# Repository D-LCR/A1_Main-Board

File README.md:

# D-LCR_A1_Main-Board
LCR Meter Analogue Main Board

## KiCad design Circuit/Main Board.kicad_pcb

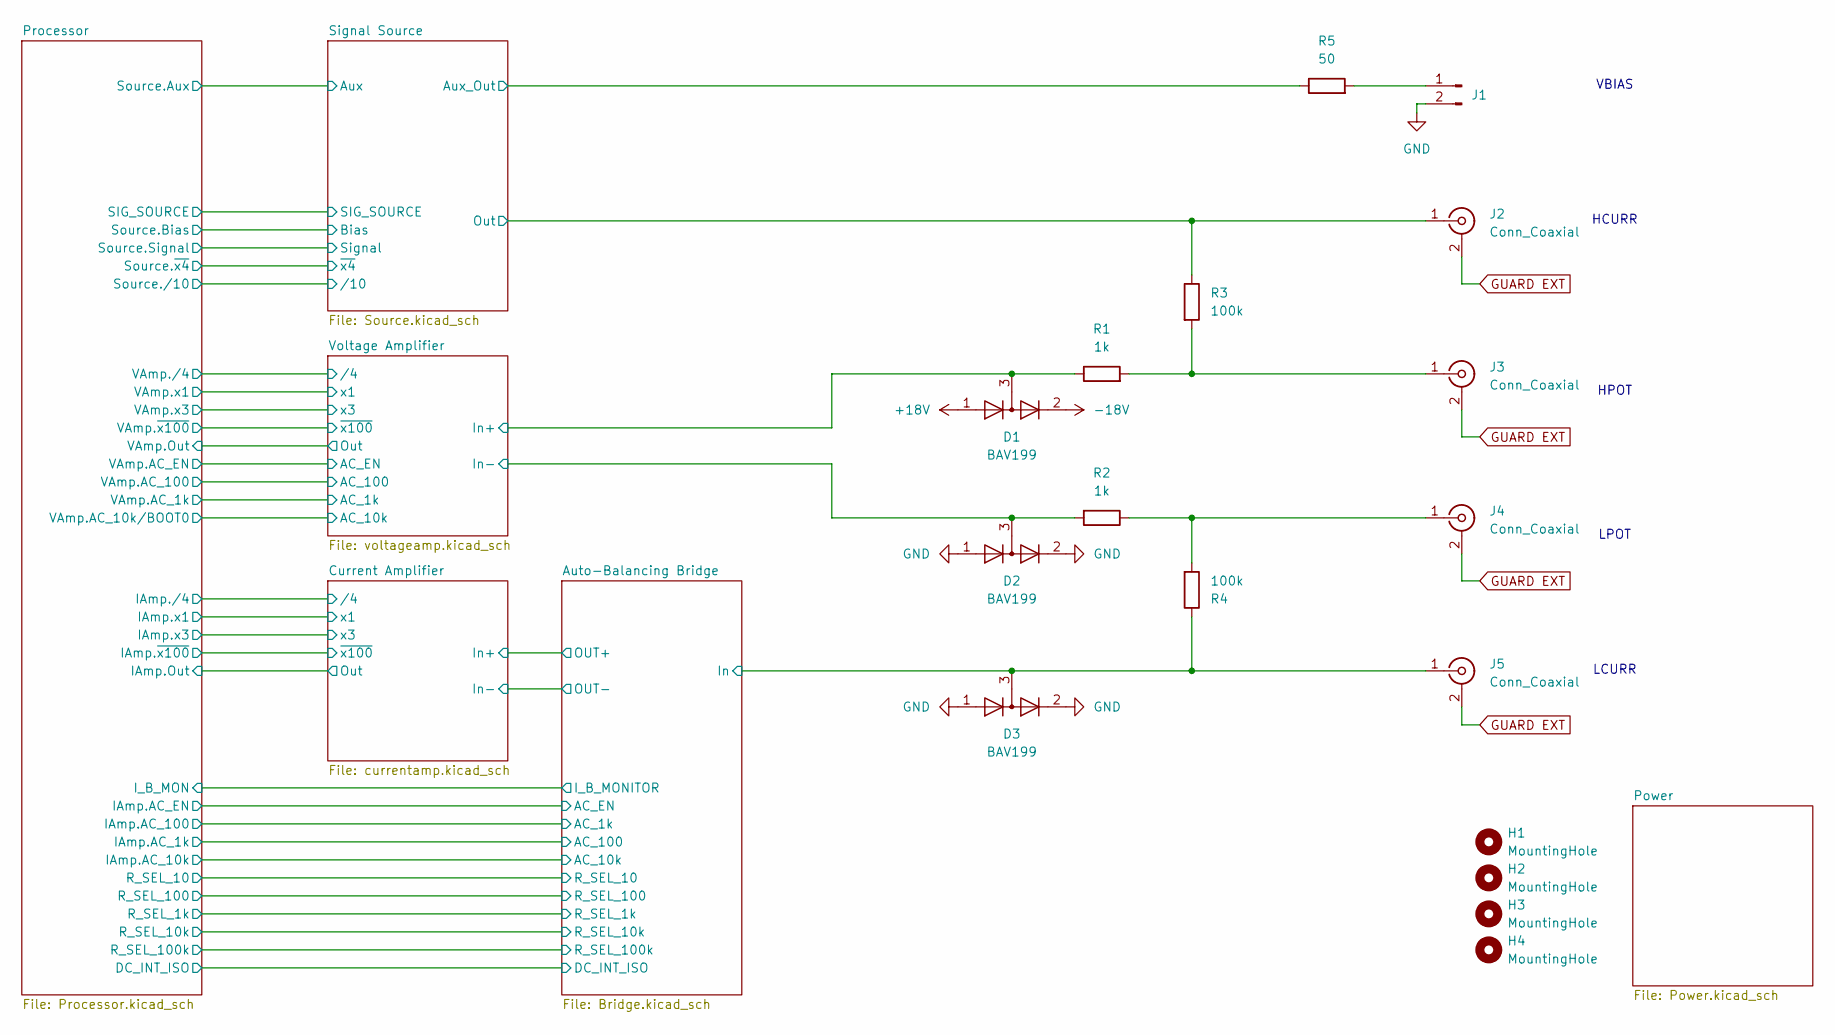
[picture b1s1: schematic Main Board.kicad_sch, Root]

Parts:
D1, D2, D3: BAV199; SOT-23
H1, H2, H3, H4: MountingHole; MountingHole_3.2mm_M3
J1: Conn_01x02_Pin; Molex_KK-254_AE-6410-02A_1x02_P2.54mm_Vertical
J2, J3, J4, J5: Conn_Coaxial; BNC_Amphenol_B6252HB-NPP3G-50_Horizontal
R1, R2: 1k; R_0805_2012Metric
R3, R4: 100k; R_0805_2012Metric
R5: 50; R_0805_2012Metric

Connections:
+18V: D1.1 (K); also elsewhere on the board
-18V: D1.2 (A); also elsewhere on the board
/Auto-Balancing Bridge/TIA_SUM: D3.3 (K), J5.1 (In), R4.1; also elsewhere on the board
/Signal Source/Aux_Out: R5.1; also elsewhere on the board
/Signal Source/Out: J2.1 (In), R3.1; also elsewhere on the board
/Voltage Amplifier/In+: D1.3 (K), R1.1; also elsewhere on the board
/Voltage Amplifier/In-: D2.3 (K), R2.2; also elsewhere on the board
GND: D2.1 (K), D2.2 (A), D3.1 (K), D3.2 (A), J1.2; also elsewhere on the board
GUARD EXT: J2.2 (Ext), J3.2 (Ext), J4.2 (Ext), J5.2 (Ext); also elsewhere on the board
unnamed: J1.1, R5.2
unnamed: J3.1 (In), R1.2, R3.2
unnamed: J4.1 (In), R2.1, R4.2

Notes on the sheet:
LPOT
HCURR
VBIAS
LCURR
HPOT

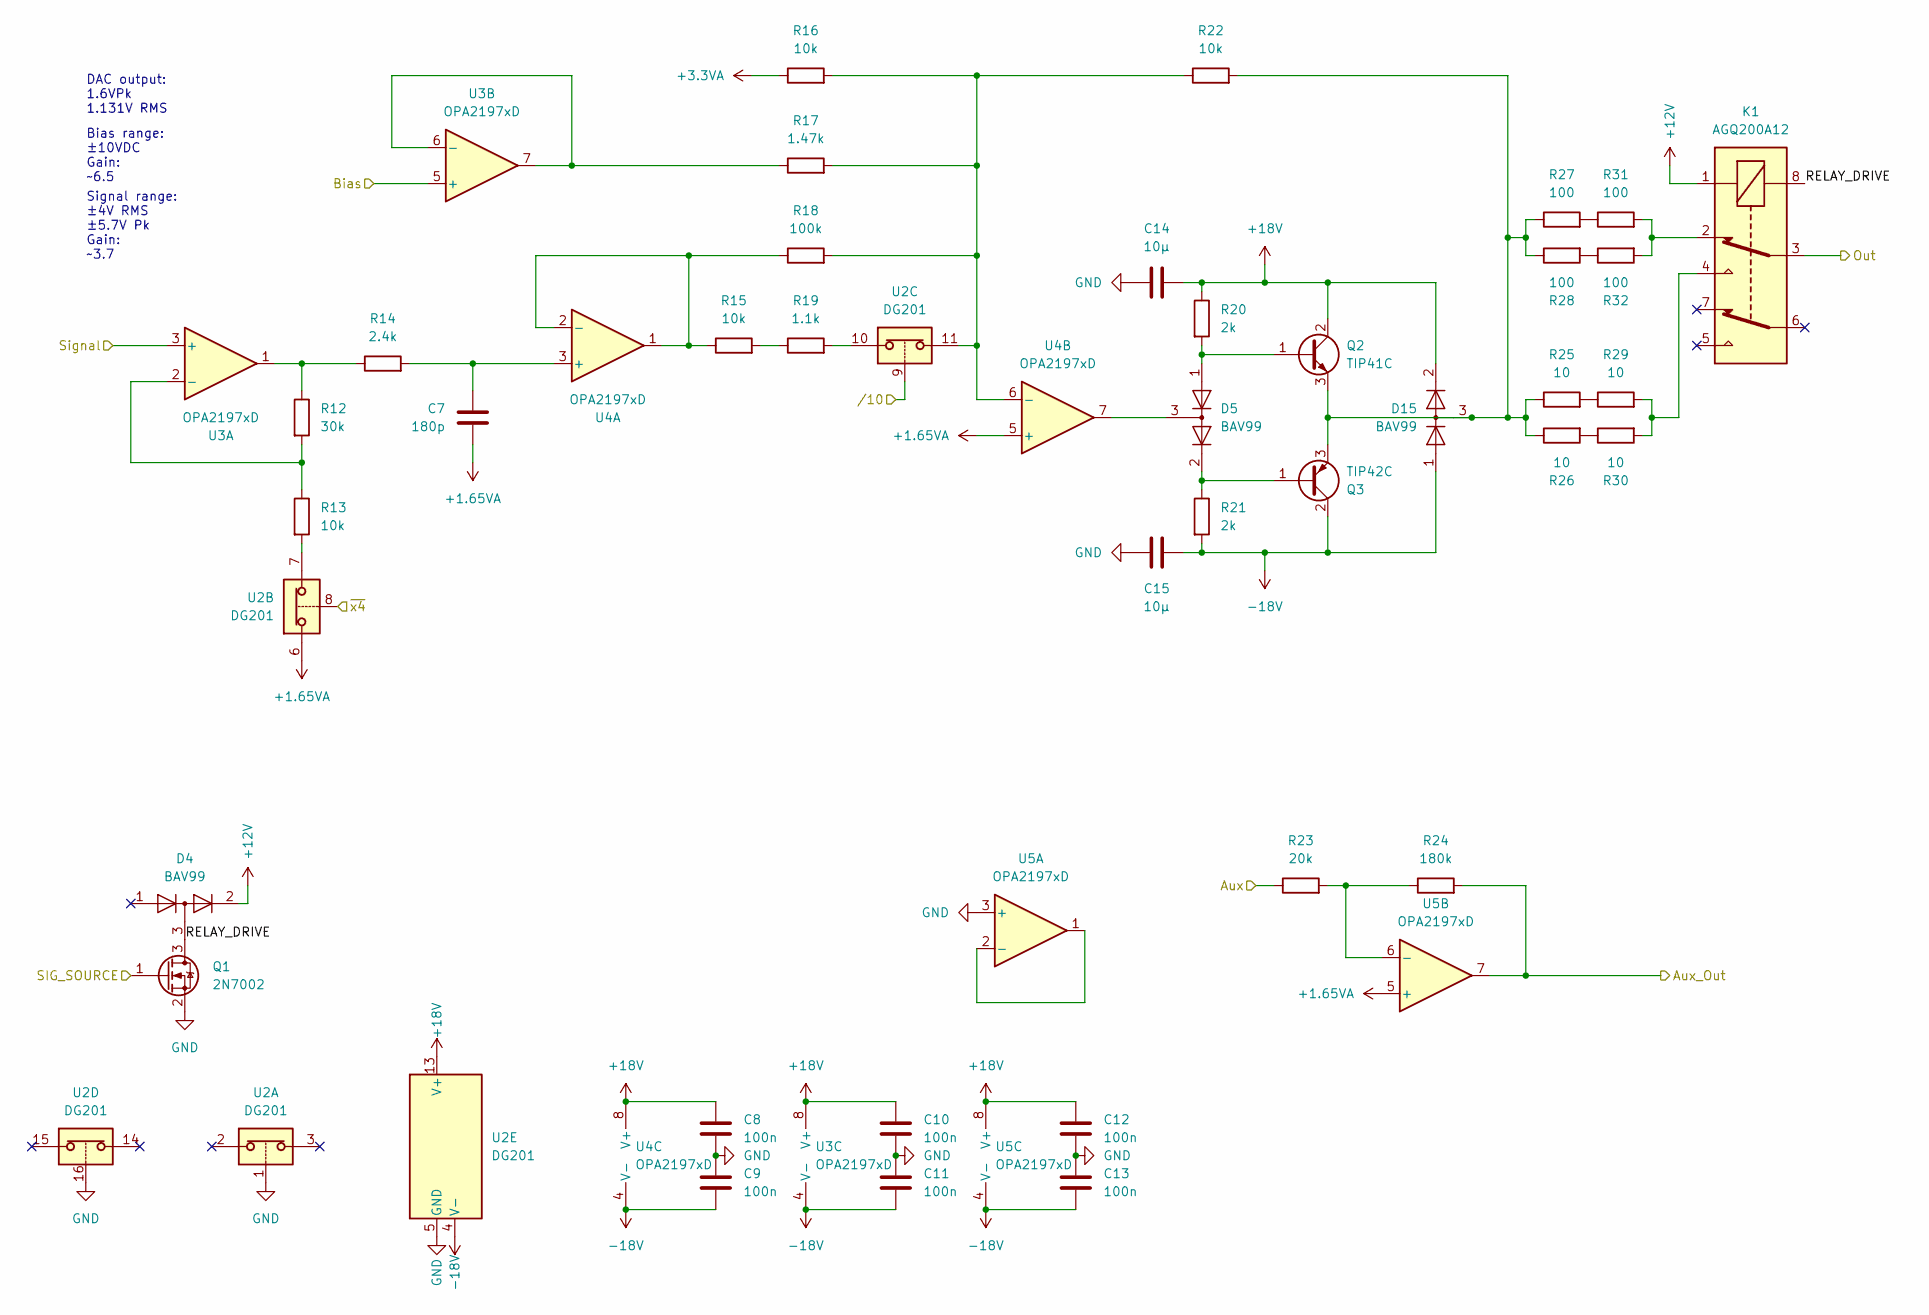
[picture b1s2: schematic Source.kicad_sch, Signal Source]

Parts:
C7: 180p; C_0805_2012Metric
C8, C9, C10, C11, C12, C13: 100n; C_0805_2012Metric
C14, C15: 10µ; C_0805_2012Metric
D4, D5, D15: BAV99; SOT-23
K1: AGQ200A12; RELAY_AGQ_A_PAN; Mouser Part Number 769-AGQ200A12
Q1: 2N7002; SOT-23
Q2: TIP41C; TO-220-3_Vertical
Q3: TIP42C; TO-220-3_Vertical
R12: 30k; R_0805_2012Metric
R13, R15, R16, R22: 10k; R_0805_2012Metric
R14: 2.4k; R_0805_2012Metric
R17: 1.47k; R_0805_2012Metric
R18: 100k; R_0805_2012Metric
R19: 1.1k; R_0805_2012Metric
R20, R21: 2k; R_0805_2012Metric
R23: 20k; R_0805_2012Metric
R24: 180k; R_0805_2012Metric
R25, R26, R29, R30: 10; R_2512_6332Metric
R27, R28, R31, R32: 100; R_0805_2012Metric
U2: DG201; SOIC-16_3.9x9.9mm_P1.27mm
U3, U4, U5: OPA2197xD; SOIC-8_3.9x4.9mm_P1.27mm

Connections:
+1.65VA: C7.2, U2.6, U4.5 (+), U5.5 (+); also elsewhere on the board
+3.3VA: R16.1; also elsewhere on the board
+12V: D4.2 (A), K1.1; also elsewhere on the board
+18V: C8.1, C10.1, C12.1, C14.2, D15.2 (A), Q2.2 (C), R20.1, U2.13 (V+), U3.8 (V+), U4.8 (V+), U5.8 (V+); also elsewhere on the board
-18V: C9.2, C11.2, C13.2, C15.2, D15.1 (K), Q3.2 (C), R21.2, U2.4 (V-), U3.4 (V-), U4.4 (V-), U5.4 (V-); also elsewhere on the board
/Processor/SIG_SOURCE: Q1.1 (G); also elsewhere on the board
/Processor/Source.Aux: R23.1; also elsewhere on the board
/Processor/Source.Bias: U3.5 (+); also elsewhere on the board
/Processor/Source.Signal: U3.3 (+); also elsewhere on the board
/Processor/Source./10: U2.9; also elsewhere on the board
/Processor/Source.~x4: U2.8; also elsewhere on the board
/Signal Source/Aux_Out: R24.2, U5.7; also elsewhere on the board
/Signal Source/Out: K1.3; also elsewhere on the board
/Signal Source/RELAY_DRIVE: D4.3 (K), K1.8, Q1.3 (D)
GND: C8.2, C9.1, C10.2, C11.1, C12.2, C13.1, C14.1, C15.1, Q1.2 (S), U2.1, U2.5 (GND), U2.16, U5.3 (+); also elsewhere on the board
unnamed: D5.2 (A), Q3.1 (B), R21.1
unnamed: D5.3 (K), U4.7
unnamed: K1.2, R31.2, R32.2
unnamed: K1.4, R29.2, R30.2
unnamed: D5.1 (K), Q2.1 (B), R20.2
unnamed: D15.3 (K), Q2.3 (E), Q3.3 (E), R22.2, R25.1, R26.1, R27.1, R28.1
unnamed: R12.1, R14.1, U3.1
unnamed: R13.2, U2.7
unnamed: R15.2, R19.1
unnamed: R19.2, U2.10
unnamed: R25.2, R29.1
unnamed: R26.2, R30.1
unnamed: R27.2, R31.1
unnamed: R28.2, R32.1
unnamed: R12.2, R13.1, U3.2 (-)
unnamed: R17.1, U3.6 (-), U3.7
unnamed: C7.1, R14.2, U4.3 (+)
unnamed: R15.1, R18.1, U4.1, U4.2 (-)
unnamed: R16.2, R17.2, R18.2, R22.1, U2.11, U4.6 (-)
unnamed: U5.1, U5.2 (-)
unnamed: R23.2, R24.1, U5.6 (-)

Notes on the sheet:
Bias range: ±10VDC Gain: ~6.5
DAC output: 1.6VPk 1.131V RMS
Signal range: ±4V RMS ±5.7V Pk Gain: ~3.7

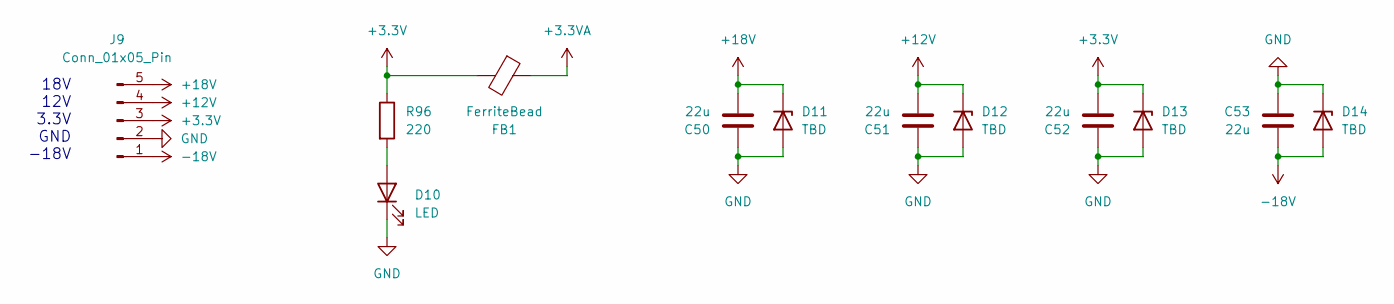
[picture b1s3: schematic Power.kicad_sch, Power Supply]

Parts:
C50, C51, C52, C53: 22u; C_1210_3225Metric
D10: LED; LED_0805_2012Metric
D11, D12, D13, D14: TBD; D_SMA
FB1: FerriteBead; L_0805_2012Metric
J9: Conn_01x05_Pin; Molex_KK-254_AE-6410-05A_1x05_P2.54mm_Vertical
R96: 220; R_0805_2012Metric

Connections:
+3.3V: C52.2, D13.1 (K), FB1.2, J9.3, R96.1; also elsewhere on the board
+3.3VA: FB1.1; also elsewhere on the board
+12V: C51.2, D12.1 (K), J9.4; also elsewhere on the board
+18V: C50.2, D11.1 (K), J9.5; also elsewhere on the board
-18V: C53.1, D14.2 (A), J9.1; also elsewhere on the board
GND: C50.1, C51.1, C52.1, C53.2, D10.1 (K), D11.2 (A), D12.2 (A), D13.2 (A), D14.1 (K), J9.2; also elsewhere on the board
unnamed: D10.2 (A), R96.2

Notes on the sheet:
18V 12V 3.3V GND -18V

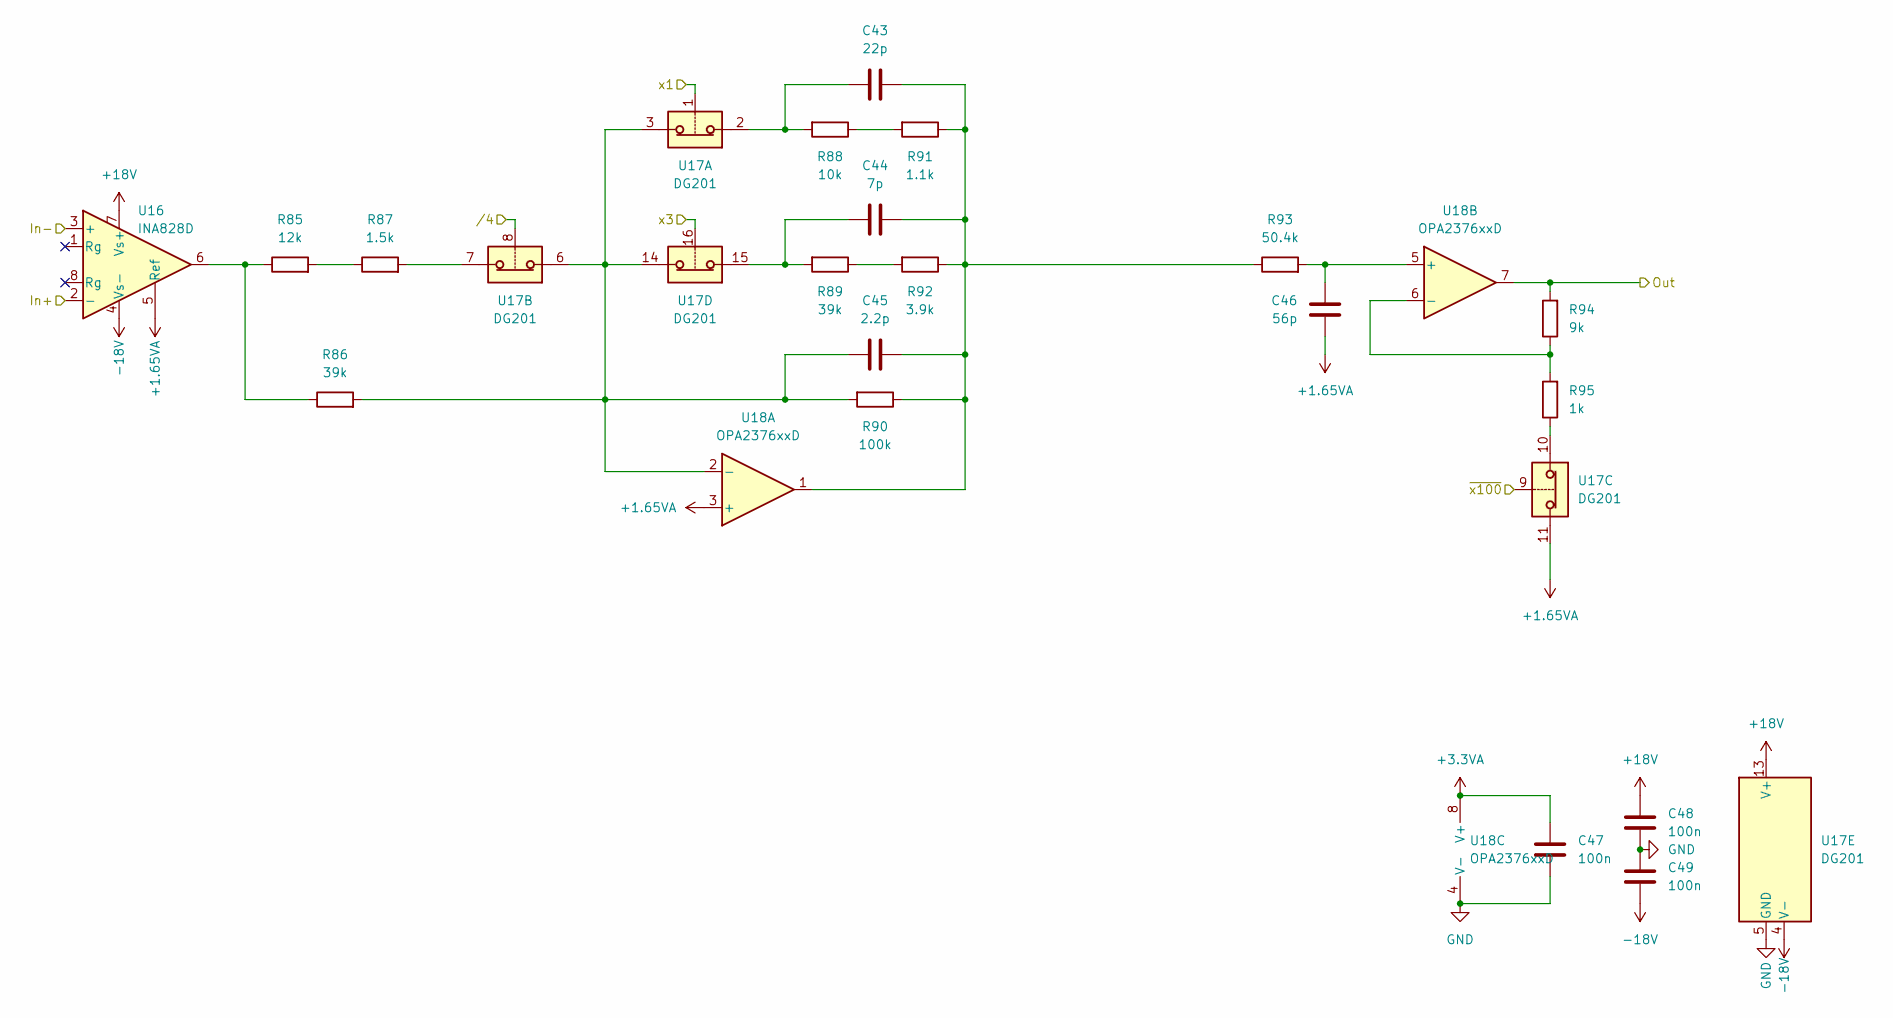
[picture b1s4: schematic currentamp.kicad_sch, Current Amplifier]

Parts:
C43: 22p; C_0805_2012Metric
C44: 7p; C_0805_2012Metric
C45: 2.2p; C_0805_2012Metric
C46: 56p; C_0805_2012Metric
C47, C48, C49: 100n; C_0805_2012Metric
R85: 12k; R_0805_2012Metric
R86, R89: 39k; R_0805_2012Metric
R87: 1.5k; R_0805_2012Metric
R88: 10k; R_0805_2012Metric
R90: 100k; R_0805_2012Metric
R91: 1.1k; R_0805_2012Metric
R92: 3.9k; R_0805_2012Metric
R93: 50.4k; R_0805_2012Metric
R94: 9k; R_0805_2012Metric
R95: 1k; R_0805_2012Metric
U16: INA828D; SOIC-8_3.9x4.9mm_P1.27mm
U17: DG201; SOIC-16_3.9x9.9mm_P1.27mm
U18: OPA2376xxD; SOIC-8_3.9x4.9mm_P1.27mm

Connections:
+1.65VA: C46.2, U16.5 (Ref), U17.11, U18.3 (+); also elsewhere on the board
+3.3VA: C47.1, U18.8 (V+); also elsewhere on the board
+18V: C48.1, U16.7 (Vs+), U17.13 (V+); also elsewhere on the board
-18V: C49.2, U16.4 (Vs-), U17.4 (V-); also elsewhere on the board
/Auto-Balancing Bridge/OUT+: U16.2 (-); also elsewhere on the board
/Auto-Balancing Bridge/TIA_SUM: U16.3 (+); also elsewhere on the board
/Current Amplifier/Out: R94.2, U18.7; also elsewhere on the board
/Current Amplifier/x1: U17.1; also elsewhere on the board
/Current Amplifier/x3: U17.16; also elsewhere on the board
/Current Amplifier//4: U17.8; also elsewhere on the board
/Current Amplifier/~x100: U17.9; also elsewhere on the board
GND: C47.2, C48.2, C49.1, U17.5 (GND), U18.4 (V-); also elsewhere on the board
unnamed: C43.1, R88.2, U17.2
unnamed: C43.2, C44.2, C45.2, R90.1, R91.1, R92.1, R93.1, U18.1
unnamed: C44.1, R89.2, U17.15
unnamed: R85.1, R86.1, U16.6
unnamed: R85.2, R87.1
unnamed: R87.2, U17.7
unnamed: R88.1, R91.2
unnamed: R89.1, R92.2
unnamed: R95.1, U17.10
unnamed: C45.1, R86.2, R90.2, U17.3, U17.6, U17.14, U18.2 (-)
unnamed: C46.1, R93.2, U18.5 (+)
unnamed: R94.1, R95.2, U18.6 (-)

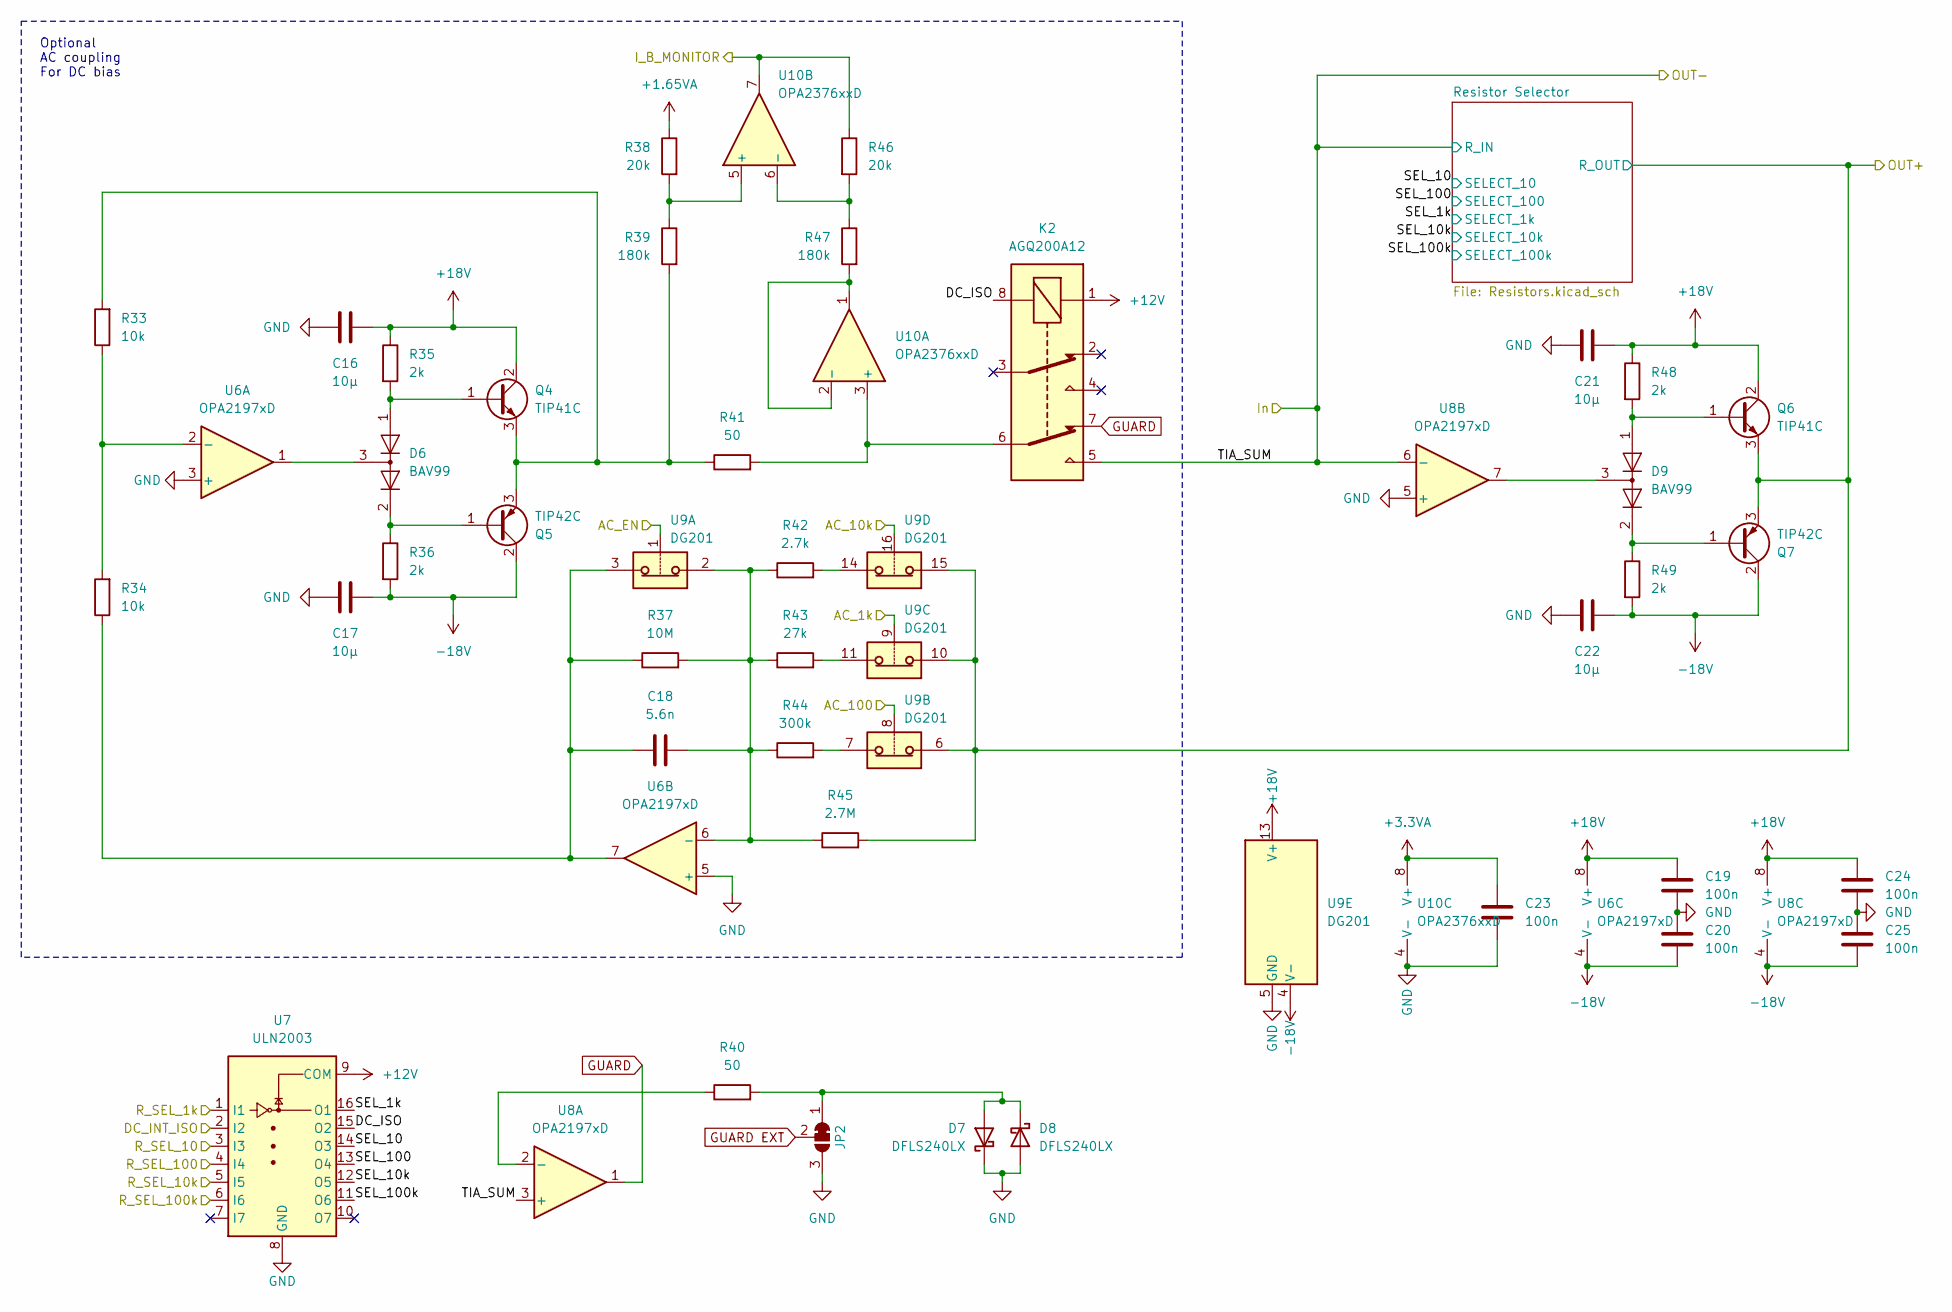
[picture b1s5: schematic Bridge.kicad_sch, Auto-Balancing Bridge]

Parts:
C16, C17, C21, C22: 10µ; C_0805_2012Metric
C18: 5.6n; C_0805_2012Metric
C19, C20, C23, C24, C25: 100n; C_0805_2012Metric
D6, D9: BAV99; SOT-23
D7, D8: DFLS240LX; D_PowerDI-123
JP2: SolderJumper_3_Bridged12; SolderJumper-3_P1.3mm_Bridged12_RoundedPad1.0x1.5mm
K2: AGQ200A12; RELAY_AGQ_A_PAN; Mouser Part Number 769-AGQ200A12
Q4, Q6: TIP41C; TO-220-3_Vertical
Q5, Q7: TIP42C; TO-220-3_Vertical
R33, R34: 10k; R_0805_2012Metric
R35, R36, R48, R49: 2k; R_0805_2012Metric
R37: 10M; R_0805_2012Metric
R38, R46: 20k; R_0805_2012Metric
R39, R47: 180k; R_0805_2012Metric
R40, R41: 50; R_0805_2012Metric
R42: 2.7k; R_0805_2012Metric
R43: 27k; R_0805_2012Metric
R44: 300k; R_0805_2012Metric
R45: 2.7M; R_0805_2012Metric
U6, U8: OPA2197xD; SOIC-8_3.9x4.9mm_P1.27mm
U7: ULN2003; SOIC-16_3.9x9.9mm_P1.27mm
U9: DG201; SOIC-16_3.9x9.9mm_P1.27mm
U10: OPA2376xxD; SOIC-8_3.9x4.9mm_P1.27mm

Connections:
+1.65VA: R38.1; also elsewhere on the board
+3.3VA: C23.1, U10.8 (V+); also elsewhere on the board
+12V: K2.1, U7.9 (COM); also elsewhere on the board
+18V: C16.2, C19.1, C21.2, C24.1, Q4.2 (C), Q6.2 (C), R35.1, R48.1, U6.8 (V+), U8.8 (V+), U9.13 (V+); also elsewhere on the board
-18V: C17.2, C20.2, C22.2, C25.2, Q5.2 (C), Q7.2 (C), R36.2, R49.2, U6.4 (V-), U8.4 (V-), U9.4 (V-); also elsewhere on the board
/Auto-Balancing Bridge/AC_1k: U9.9; also elsewhere on the board
/Auto-Balancing Bridge/AC_10k: U9.16; also elsewhere on the board
/Auto-Balancing Bridge/AC_100: U9.8; also elsewhere on the board
/Auto-Balancing Bridge/AC_EN: U9.1; also elsewhere on the board
/Auto-Balancing Bridge/DC_INT_ISO: U7.2 (I2); also elsewhere on the board
/Auto-Balancing Bridge/DC_ISO: K2.8, U7.15 (O2)
/Auto-Balancing Bridge/I_B_MONITOR: R46.1, U10.7; also elsewhere on the board
/Auto-Balancing Bridge/OUT+: Q6.3 (E), Q7.3 (E), R45.2, U9.6, U9.10, U9.15; also elsewhere on the board
/Auto-Balancing Bridge/R_SEL_1k: U7.1 (I1); also elsewhere on the board
/Auto-Balancing Bridge/R_SEL_10: U7.3 (I3); also elsewhere on the board
/Auto-Balancing Bridge/R_SEL_10k: U7.5 (I5); also elsewhere on the board
/Auto-Balancing Bridge/R_SEL_100: U7.4 (I4); also elsewhere on the board
/Auto-Balancing Bridge/R_SEL_100k: U7.6 (I6); also elsewhere on the board
/Auto-Balancing Bridge/SEL_1k: U7.16 (O1); also elsewhere on the board
/Auto-Balancing Bridge/SEL_10: U7.14 (O3); also elsewhere on the board
/Auto-Balancing Bridge/SEL_10k: U7.12 (O5); also elsewhere on the board
/Auto-Balancing Bridge/SEL_100: U7.13 (O4); also elsewhere on the board
/Auto-Balancing Bridge/SEL_100k: U7.11 (O6); also elsewhere on the board
/Auto-Balancing Bridge/TIA_SUM: K2.5, U8.3 (+), U8.6 (-); also elsewhere on the board
GND: C16.1, C17.1, C19.2, C20.1, C21.1, C22.1, C23.2, C24.2, C25.1, D7.1 (K), D8.2 (A), JP2.3 (B), U6.3 (+), U6.5 (+), U7.8 (GND), U8.5 (+), U9.5 (GND), U10.4 (V-); also elsewhere on the board
GUARD: K2.7, U8.1; also elsewhere on the board
GUARD EXT: JP2.2 (C); also elsewhere on the board
unnamed: C18.1, R34.1, R37.1, U6.7, U9.3
unnamed: D6.2 (A), Q5.1 (B), R36.1
unnamed: D6.3 (K), U6.1
unnamed: D7.2 (A), D8.1 (K), JP2.1 (A), R40.2
unnamed: D9.2 (A), Q7.1 (B), R49.1
unnamed: D9.3 (K), U8.7
unnamed: D6.1 (K), Q4.1 (B), R35.2
unnamed: Q4.3 (E), Q5.3 (E), R33.2, R39.2, R41.1
unnamed: D9.1 (K), Q6.1 (B), R48.2
unnamed: R42.2, U9.14
unnamed: R43.2, U9.11
unnamed: R44.2, U9.7
unnamed: R33.1, R34.2, U6.2 (-)
unnamed: C18.2, R37.2, R42.1, R43.1, R44.1, R45.1, U6.6 (-), U9.2
unnamed: R40.1, U8.2 (-)
unnamed: K2.6, R41.2, U10.3 (+)
unnamed: R47.2, U10.1, U10.2 (-)
unnamed: R38.2, R39.1, U10.5 (+)
unnamed: R46.2, R47.1, U10.6 (-)

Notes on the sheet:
Optional AC coupling For DC bias

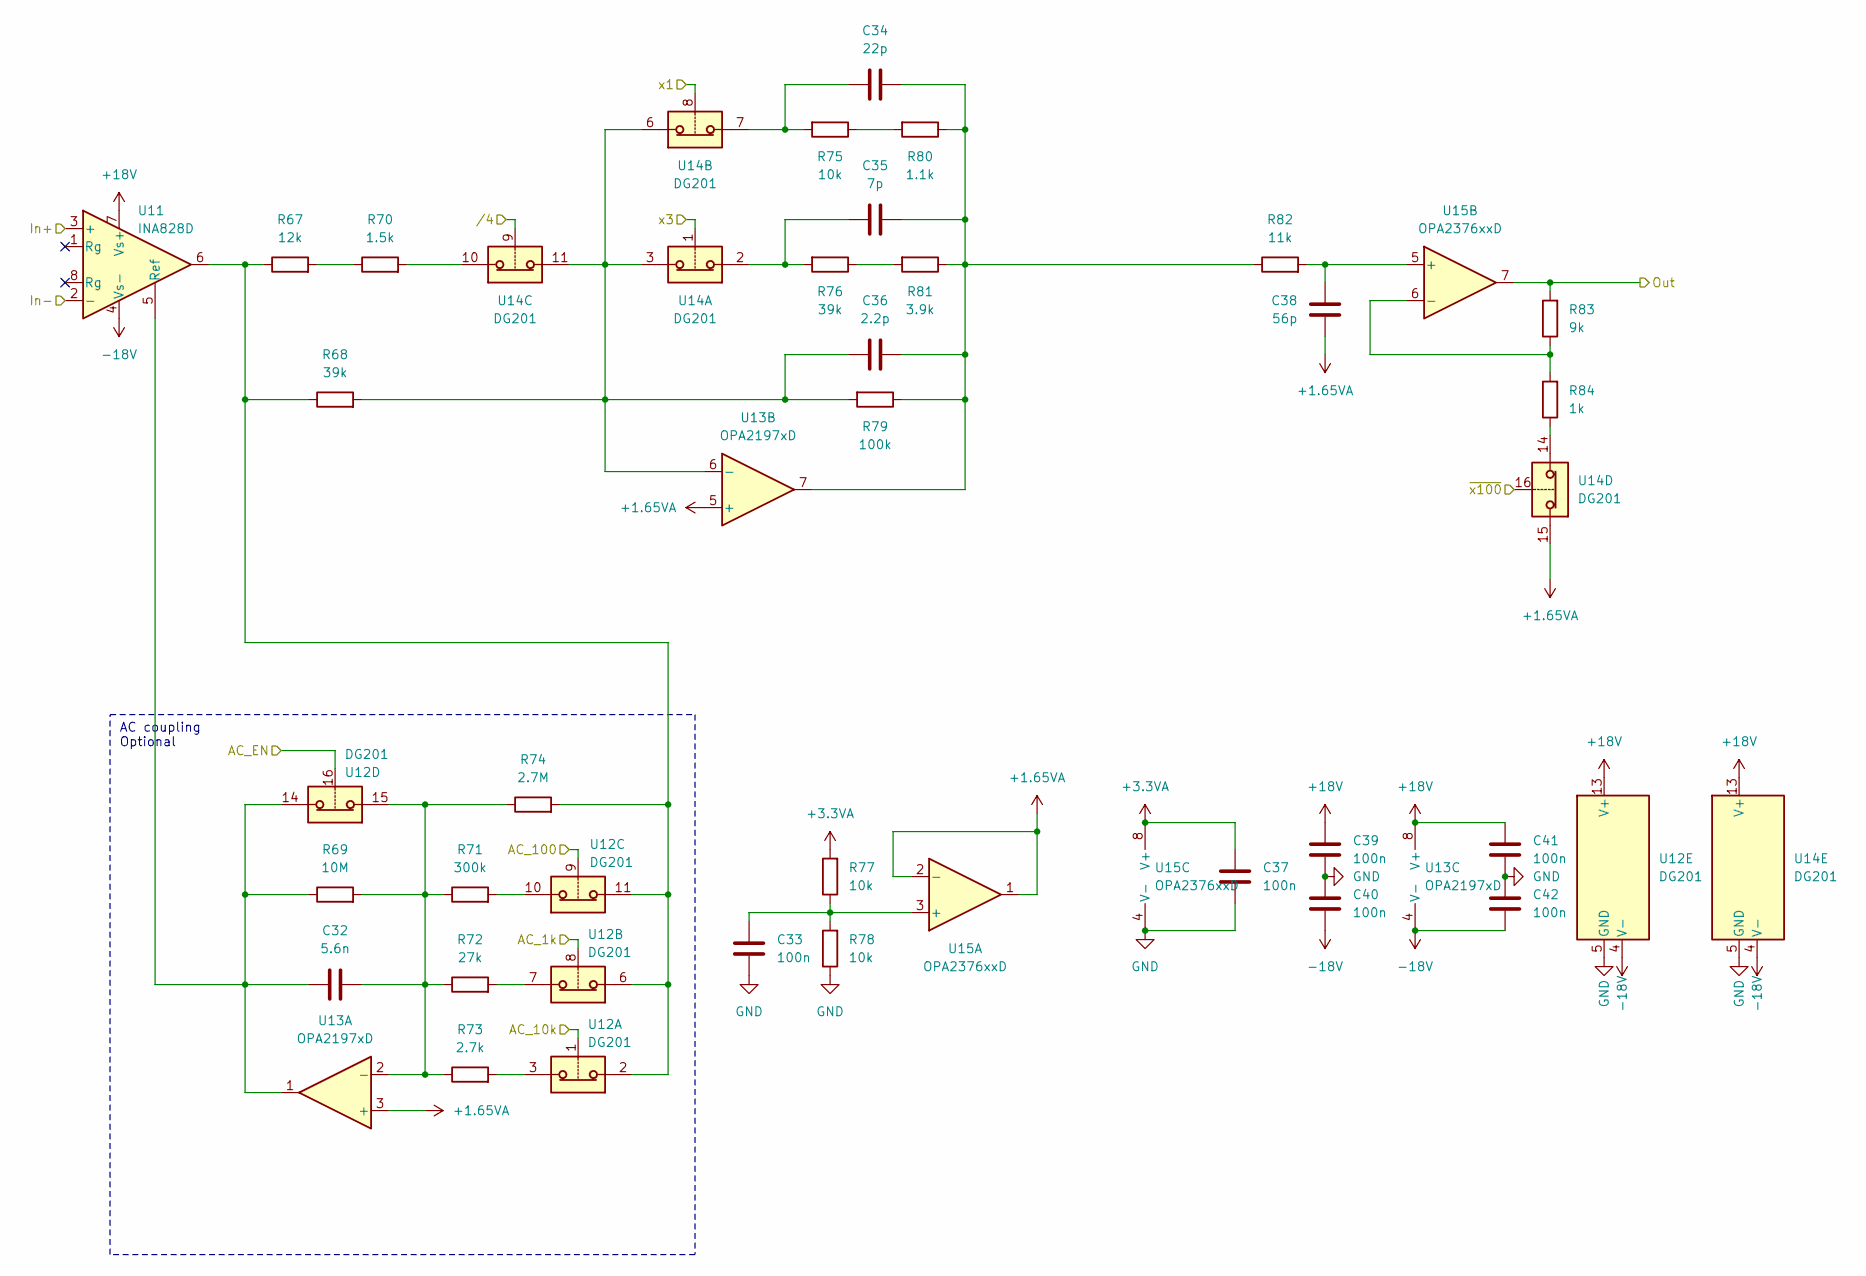
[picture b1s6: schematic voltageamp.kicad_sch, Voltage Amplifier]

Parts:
C32: 5.6n; C_0805_2012Metric
C33, C37, C39, C40, C41, C42: 100n; C_0805_2012Metric
C34: 22p; C_0805_2012Metric
C35: 7p; C_0805_2012Metric
C36: 2.2p; C_0805_2012Metric
C38: 56p; C_0805_2012Metric
R67: 12k; R_0805_2012Metric
R68, R76: 39k; R_0805_2012Metric
R69: 10M; R_0805_2012Metric
R70: 1.5k; R_0805_2012Metric
R71: 300k; R_0805_2012Metric
R72: 27k; R_0805_2012Metric
R73: 2.7k; R_0805_2012Metric
R74: 2.7M; R_0805_2012Metric
R75, R77, R78: 10k; R_0805_2012Metric
R79: 100k; R_0805_2012Metric
R80: 1.1k; R_0805_2012Metric
R81: 3.9k; R_0805_2012Metric
R82: 11k; R_0805_2012Metric
R83: 9k; R_0805_2012Metric
R84: 1k; R_0805_2012Metric
U11: INA828D; SOIC-8_3.9x4.9mm_P1.27mm
U12, U14: DG201; SOIC-16_3.9x9.9mm_P1.27mm
U13: OPA2197xD; SOIC-8_3.9x4.9mm_P1.27mm
U15: OPA2376xxD; SOIC-8_3.9x4.9mm_P1.27mm

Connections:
+1.65VA: C38.2, U13.3 (+), U13.5 (+), U14.15, U15.1, U15.2 (-); also elsewhere on the board
+3.3VA: C37.1, R77.2, U15.8 (V+); also elsewhere on the board
+18V: C39.1, C41.1, U11.7 (Vs+), U12.13 (V+), U13.8 (V+), U14.13 (V+); also elsewhere on the board
-18V: C40.2, C42.2, U11.4 (Vs-), U12.4 (V-), U13.4 (V-), U14.4 (V-); also elsewhere on the board
/Processor/VAmp.AC_1k: U12.8; also elsewhere on the board
/Processor/VAmp.AC_10k/BOOT0: U12.1; also elsewhere on the board
/Processor/VAmp.AC_100: U12.9; also elsewhere on the board
/Processor/VAmp.AC_EN: U12.16; also elsewhere on the board
/Processor/VAmp.Out: R83.2, U15.7; also elsewhere on the board
/Processor/VAmp.x1: U14.8; also elsewhere on the board
/Processor/VAmp.x3: U14.1; also elsewhere on the board
/Processor/VAmp./4: U14.9; also elsewhere on the board
/Processor/VAmp.~x100: U14.16; also elsewhere on the board
/Voltage Amplifier/In+: U11.3 (+); also elsewhere on the board
/Voltage Amplifier/In-: U11.2 (-); also elsewhere on the board
GND: C33.2, C37.2, C39.2, C40.1, C41.2, C42.1, R78.1, U12.5 (GND), U14.5 (GND), U15.4 (V-); also elsewhere on the board
unnamed: C34.1, R75.2, U14.7
unnamed: C34.2, C35.2, C36.2, R79.1, R80.1, R81.1, R82.1, U13.7
unnamed: C35.1, R76.2, U14.2
unnamed: R67.1, R68.1, R74.2, U11.6, U12.2, U12.6, U12.11
unnamed: R67.2, R70.1
unnamed: R70.2, U14.10
unnamed: R71.2, U12.10
unnamed: R72.2, U12.7
unnamed: R73.2, U12.3
unnamed: R75.1, R80.2
unnamed: R76.1, R81.2
unnamed: R84.1, U14.14
unnamed: C32.1, R69.1, U11.5 (Ref), U12.14, U13.1
unnamed: C32.2, R69.2, R71.1, R72.1, R73.1, R74.1, U12.15, U13.2 (-)
unnamed: C36.1, R68.2, R79.2, U13.6 (-), U14.3, U14.6, U14.11
unnamed: C33.1, R77.1, R78.2, U15.3 (+)
unnamed: C38.1, R82.2, U15.5 (+)
unnamed: R83.1, R84.2, U15.6 (-)

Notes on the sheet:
AC coupling Optional
